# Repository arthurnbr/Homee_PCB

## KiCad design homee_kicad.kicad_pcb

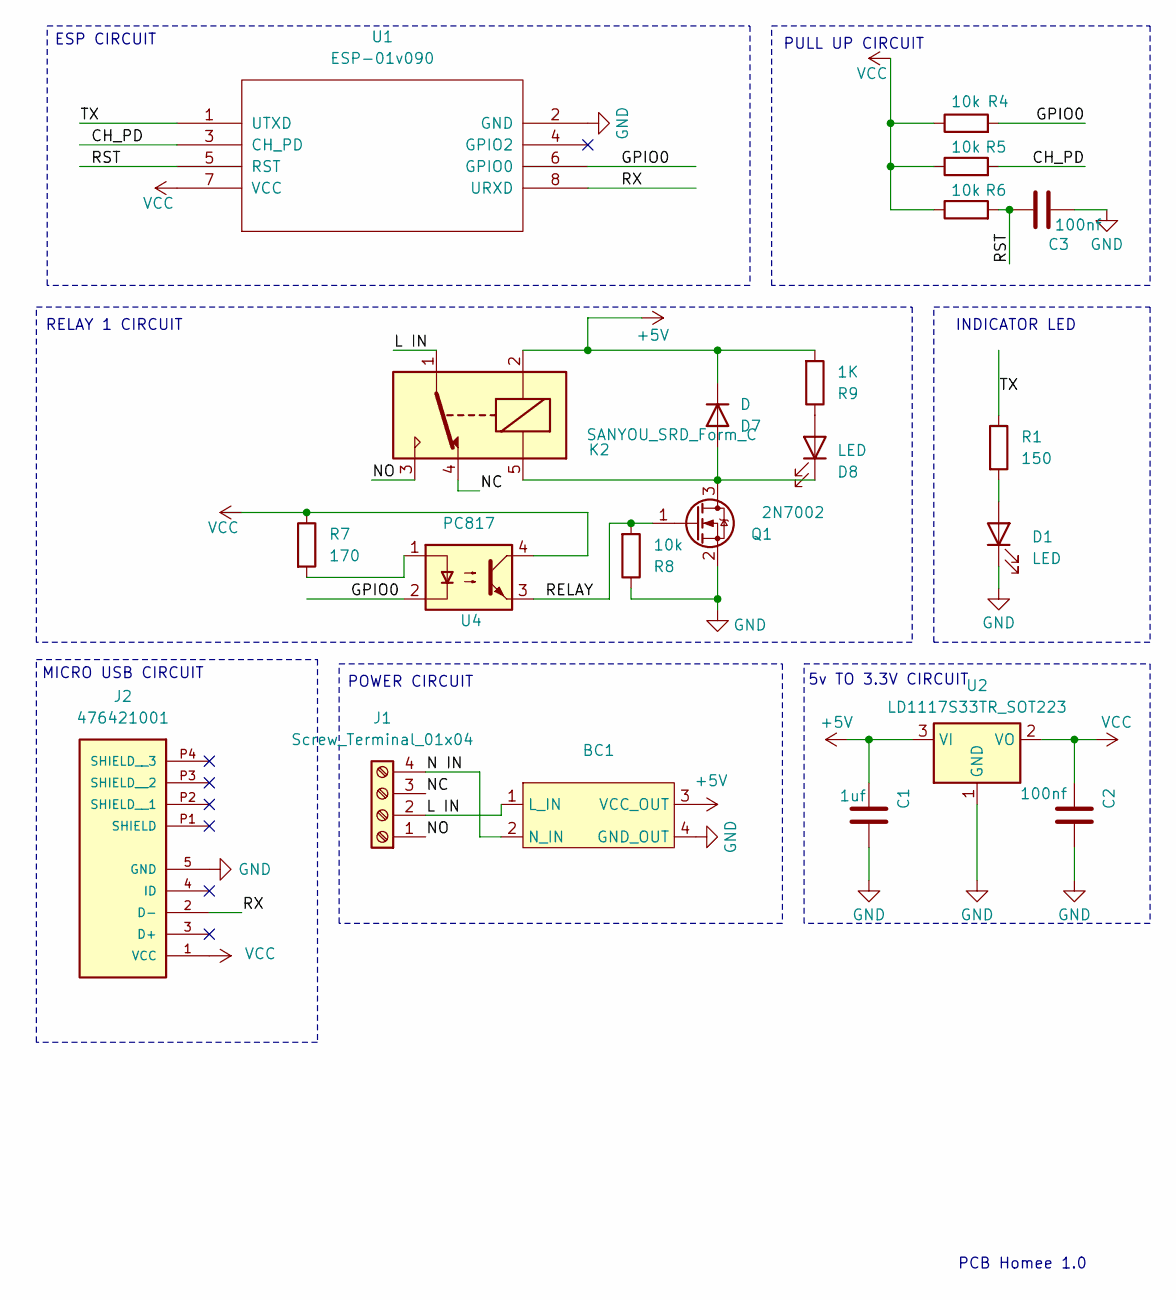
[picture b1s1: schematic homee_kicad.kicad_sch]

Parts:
BC1: Buck Connect
C1: 1uf; C_1210_3225Metric; MPN C5189828
C2, C3: 100nf; C_1210_3225Metric; MPN C7393836
D1, D8: LED; LED_D3.0mm; MPN C3028821
D7: D; D_1210_3225Metric_Pad1.42x2.65mm_HandSolder; MPN C17688656
J1: Screw_Terminal_01x04; TerminalBlock_Xinya_XY308-2.54-4P_1x04_P2.54mm_Horizontal
J2: 476421001; MOLEX_476421001; PARTREV D
K2: SANYOU_SRD_Form_C; Relay_SPDT_SANYOU_SRD_Series_Form_C
Q1: 2N7002; SOT-23; MPN C5224215
R1: 150; R_0805_2012Metric_Pad1.20x1.40mm_HandSolder; MPN C5141050
R4, R5, R6, R8: 10k; R_0805_2012Metric_Pad1.20x1.40mm_HandSolder; MPN C2889342
R7: 170; R_0805_2012Metric_Pad1.20x1.40mm_HandSolder
R9: 1K; R_0805_2012Metric_Pad1.20x1.40mm_HandSolder; MPN C384390
U1: ESP-01v090; PinSocket_2x04_P2.54mm_Vertical; MPN C2977588
U2: LD1117S33TR_SOT223; SOT-223-3_TabPin2; MPN C20538888
U4: PC817; SMDIP-4_W7.62mm; MPN C2936043

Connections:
+5V: BC1.3 (VCC_OUT), C1.2, D7.1 (K), K2.2, R9.2, U2.3 (VI)
/CH_PD: R5.2, U1.3 (CH_PD)
/GPIO0: R4.2, U1.6 (GPIO0), U4.2
/L IN: BC1.1 (L_IN), J1.2, K2.1
/N IN: BC1.2 (N_IN), J1.4
/NC: J1.3, K2.4
/NO: J1.1, K2.3
/RELAY: Q1.1 (G), R8.2, U4.3
/RST: C3.1, R6.2, U1.5 (RST)
/RX: J2.2 (D-), U1.8 (URXD)
/TX: R1.1, U1.1 (UTXD)
GND: BC1.4 (GND_OUT), C1.1, C2.1, C3.2, D1.1 (K), J2.5 (GND), Q1.2 (S), R8.1, U1.2 (GND), U2.1 (GND)
unnamed: D1.2 (A), R1.2
unnamed: D7.2 (A), D8.1 (K), K2.5, Q1.3 (D)
unnamed: D8.2 (A), R9.1
unnamed: R7.2, U4.1
VCC: C2.2, J2.1 (VCC), R4.1, R5.1, R6.1, R7.1, U1.7 (VCC), U2.2 (VO), U4.4

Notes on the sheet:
INDICATOR LED
PCB Homee 1.0
MICRO USB CIRCUIT
RELAY 1 CIRCUIT
ESP CIRCUIT
PULL UP CIRCUIT
5v TO 3.3V CIRCUIT
POWER CIRCUIT

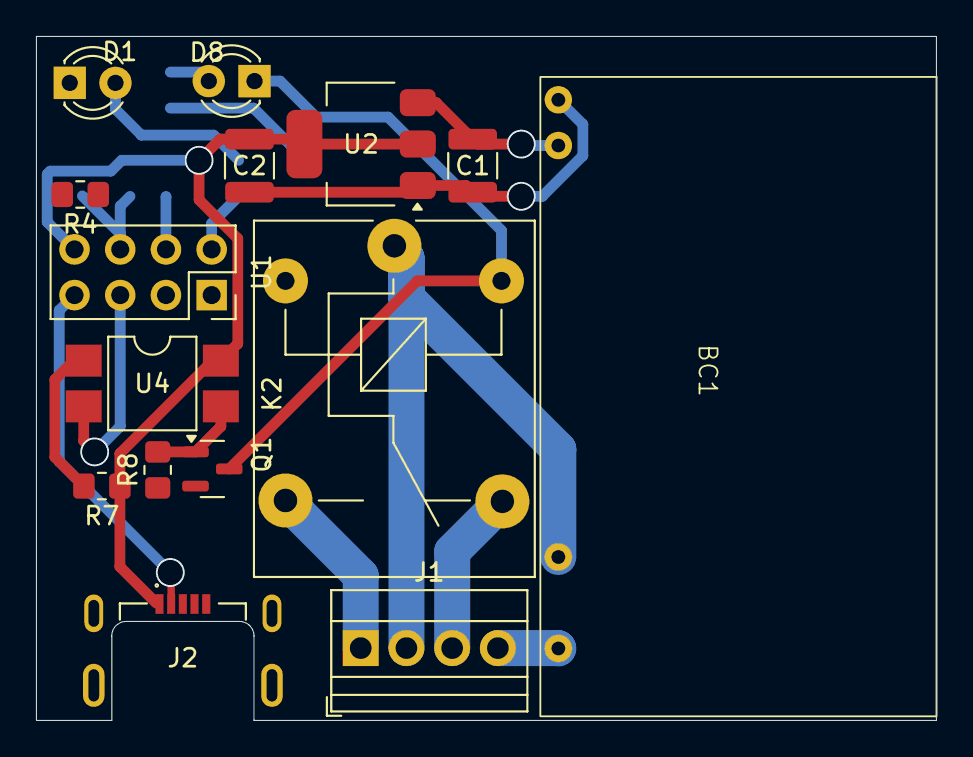
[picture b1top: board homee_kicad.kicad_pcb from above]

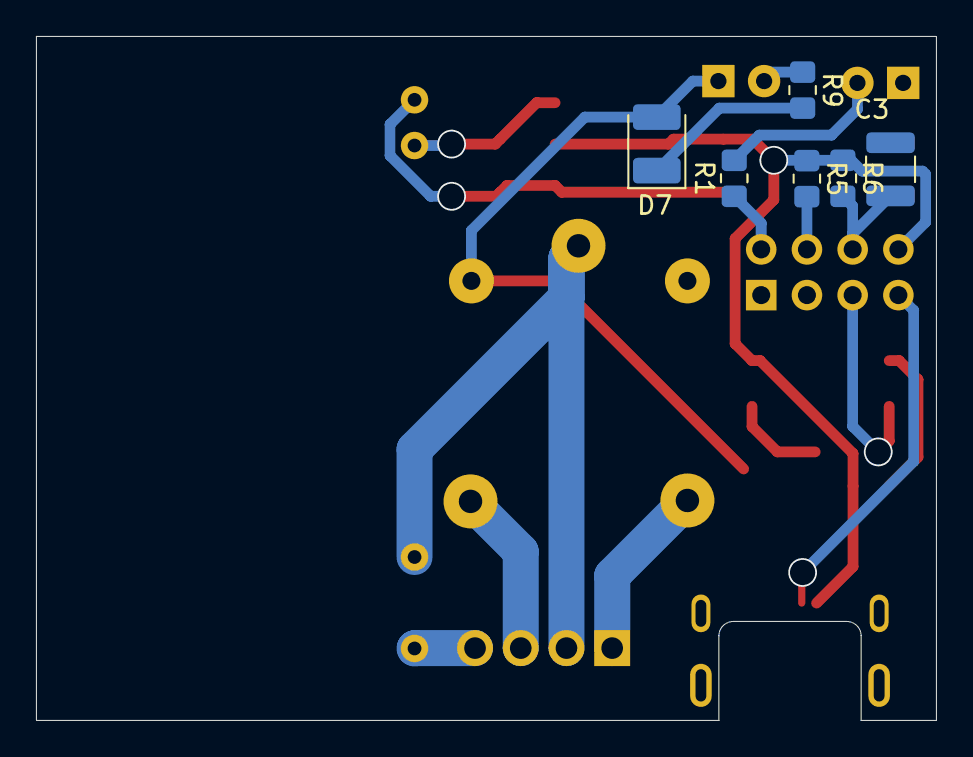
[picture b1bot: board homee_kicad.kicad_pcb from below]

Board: 2 copper layers, 50.0 x 38.0 mm, 21 parts (6 on the bottom side), 17 nets.

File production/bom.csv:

Designator,Footprint,Quantity,Value,LCSC Part #
BC1,Buck Connect,1,~,
C1,1210,1,1uf,C5189828
"C2, C3",1210,2,100nf,C7393836
"D1, D8",LED_D3.0mm,2,LED,C3028821
D7,1210,1,D,C17688656
"J1, J3","TerminalBlock_Phoenix_MKDS-1,5-2-5.08_1x02_P5.08mm_Horizontal",2,Screw_Terminal_01x02,C8269
J2,USB_Micro-B_Molex-105017-0001,1,USB_B_Micro, C234179
K2,Relay_SPST_SANYOU_SRD_Series_Form_A,1,SANYOU_SRD_Form_A,C185799
Q1,SOT-23,1,2N7002,C5224215
R1,1210,1,150,C5141050
"R4, R5, R6, R8",1210,4,10k,C2889342
R7,1210,1,170,
R9,1210,1,1K,C384390
U1,PinSocket_2x04_P2.54mm_Vertical,1,ESP-01v090,C2977588
U2,SOT-223-3_TabPin2,1,LD1117S33TR_SOT223,C20538888
U4,SMDIP-4_W7.62mm,1,PC817,C2936043

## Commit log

2024-09-17 Origin Commit
2024-09-17 Relay Circuit Usb Circuit Pull up Circuit
2024-09-19 bcp de chose
2024-09-20 hello
2024-09-20 j'ai tt fini je suis le goat (PS pas verif par le prof)
2024-09-26 inte
2024-09-26 oeoe
2024-09-27 start rework
2024-09-27 schema final rework
2024-09-27 Changed Homee footprint lib from Global Lib to Projet Lib
2024-09-27 oupsi
2024-09-27 Test W/O routes
2024-09-27 Change IO disposition
2024-09-27 UPDATED TEST W/O ROUTES
2024-09-27 JOB'S FINISHED ? JOB'S NOT FINISHED
2024-09-30 oups
2024-09-30 gained 5 min in width
2024-09-30 je croyais que j'avais fini :(
2024-10-02 PLZ BE THE LAST TIME :'(
